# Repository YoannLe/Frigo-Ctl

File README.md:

# Frigo-Ctl
Arduino controller and thermostat with touch screen for 12V Fridge Compressor. Boat, RV, motorhome. To drive Danfoss, SECOP, vitrifrigo, 101N0212 compressors control units.

Compressors RPM, start and stop could be controled by resistors values and mechanical thermostat.

To set the best ratio between compressor speed and cold generation needed, the AOE protocol was developed on high end devices. This project coud genarate AOE control on a standard unit and specials functions like manual boost, graphic touch screen and DS18B20 temperature sensors.

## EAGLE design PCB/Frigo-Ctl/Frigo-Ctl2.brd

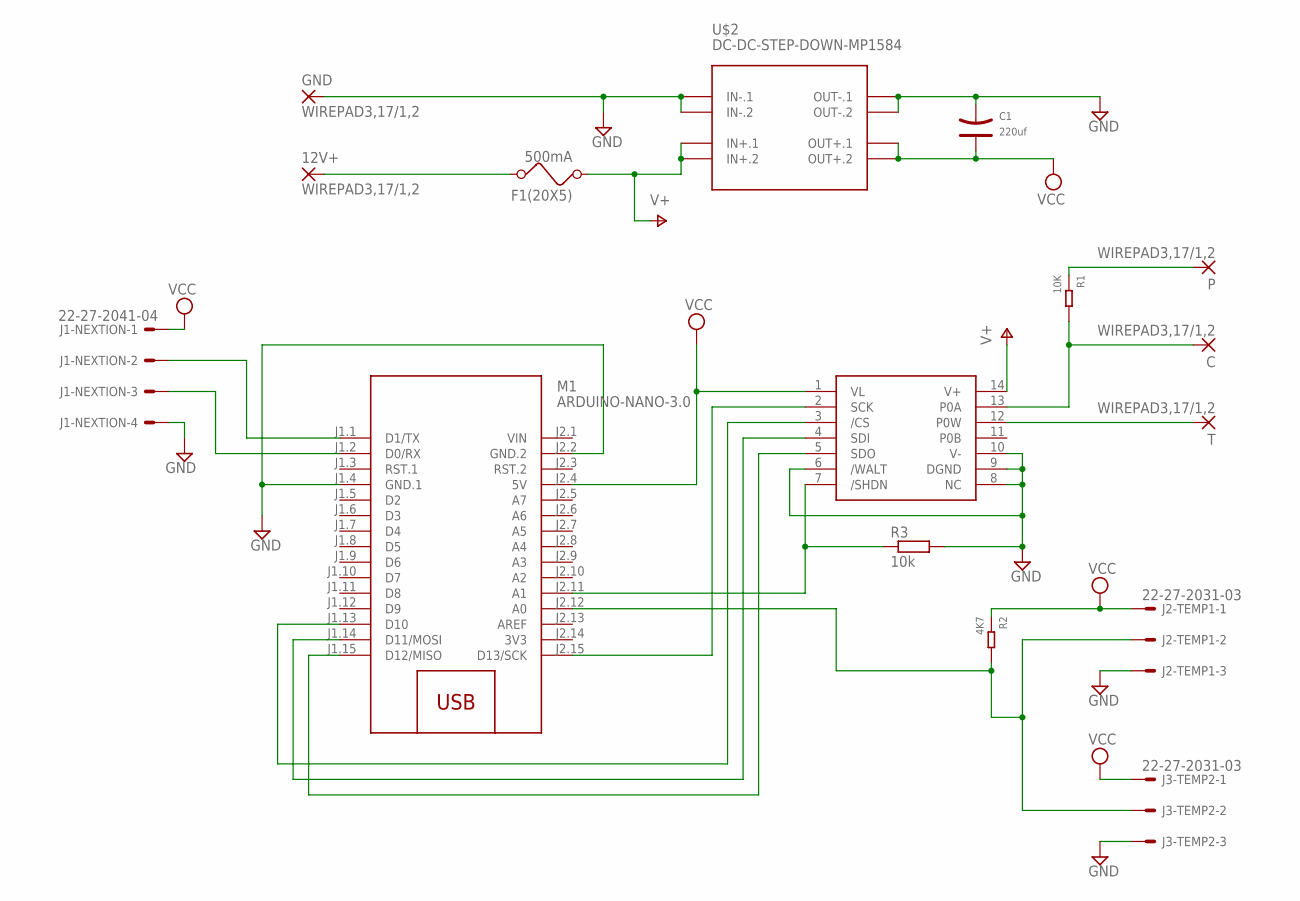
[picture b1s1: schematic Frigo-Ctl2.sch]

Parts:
12V+: WIREPAD3,17/1,2; 3,17/1,2
C: WIREPAD3,17/1,2; 3,17/1,2
C1: 220uf; PC-D5.3MM
F1(20X5): 500mA; FUSE
GND: WIREPAD3,17/1,2; 3,17/1,2
J1-NEXTION: 22-27-2041-04; 6410-04
J2-TEMP1, J3-TEMP2: 22-27-2031-03; 6410-03
M1: ARDUINO-NANO-3.0
P: WIREPAD3,17/1,2; 3,17/1,2
R1: 10K; PR-D2.3XL6.5MM
R2: 4K7; PR-D2.3XL6.5MM
R3: 10k; R1206
T: WIREPAD3,17/1,2; 3,17/1,2
U$1: MCP41HV51; TSSOP14
U$2: DC-DC-STEP-DOWN-MP1584

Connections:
3V3: M1.J2.14 (3V3)
GND: C1.-, GND.1, J1-NEXTION.4, J2-TEMP1.3, J3-TEMP2.3, M1.J1.4 (GND.1), M1.J2.2 (GND.2), R3.2, U$1.6 (/WALT), U$1.8 (NC), U$1.9 (DGND), U$1.10 (V-), U$2.IN-.1, U$2.IN-.2, U$2.OUT-.1, U$2.OUT-.2
unnamed: 12V+.1, F1(20X5).2
unnamed: M1.J2.11 (A1), R3.1, U$1.7 (/SHDN)
unnamed: J1-NEXTION.2, M1.J1.1 (D1/TX)
unnamed: J1-NEXTION.3, M1.J1.2 (D0/RX)
unnamed: C.1, R1.2, U$1.13 (P0A)
unnamed: P.1, R1.1
unnamed: M1.J1.13 (D10), U$1.3 (/CS)
unnamed: T.1, U$1.12 (P0W)
unnamed: M1.J2.15 (D13/SCK), U$1.2 (SCK)
unnamed: M1.J1.15 (D12/MISO), U$1.5 (SDO)
unnamed: M1.J1.14 (D11/MOSI), U$1.4 (SDI)
unnamed: J2-TEMP1.2, J3-TEMP2.2, M1.J2.12 (A0), R2.2
V+: F1(20X5).1, U$1.14 (V+), U$2.IN+.1, U$2.IN+.2
VCC: C1.+, J1-NEXTION.1, J2-TEMP1.1, J3-TEMP2.1, M1.J2.4 (5V), R2.1, U$1.1 (VL), U$2.OUT+.1, U$2.OUT+.2
VIN: M1.J2.1 (VIN)

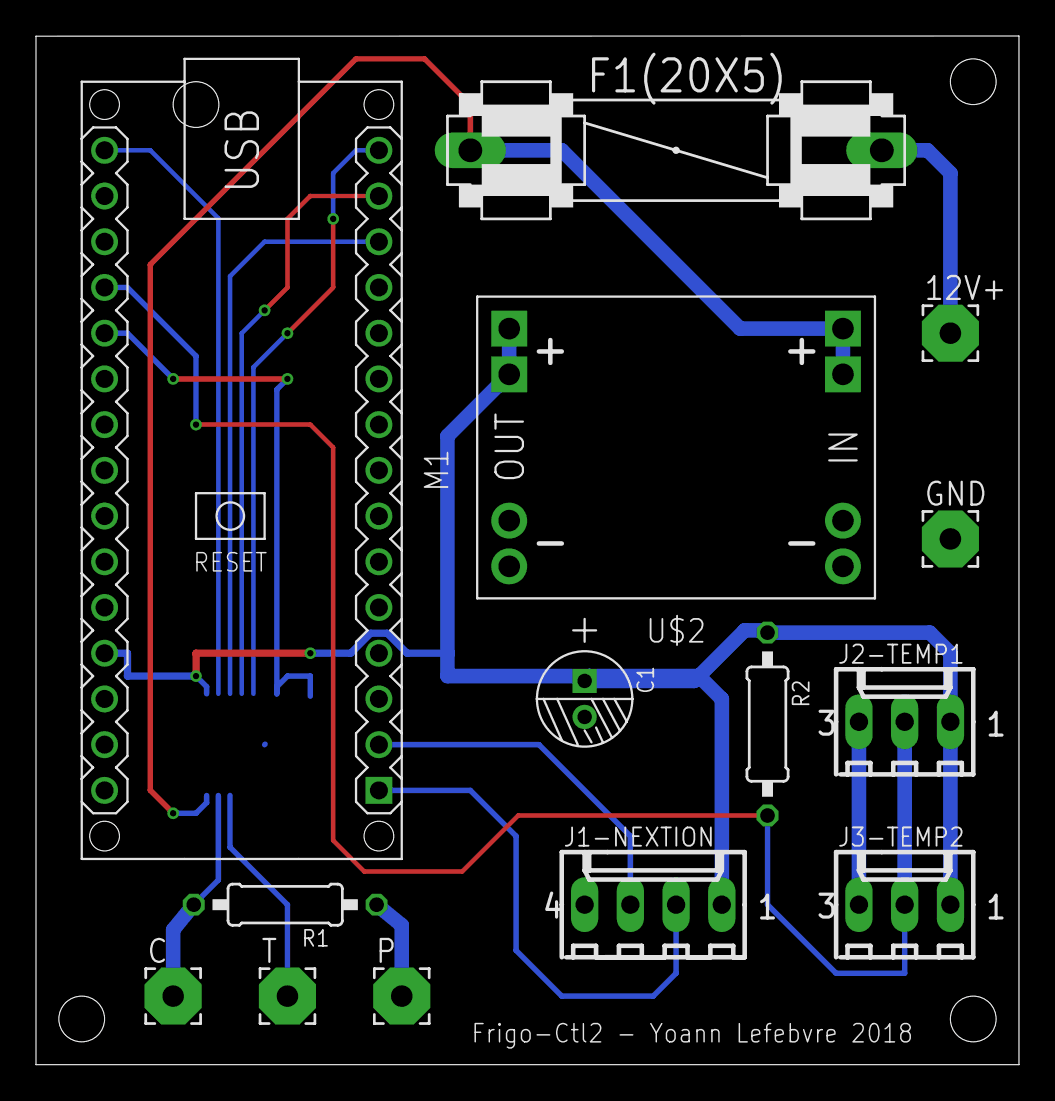
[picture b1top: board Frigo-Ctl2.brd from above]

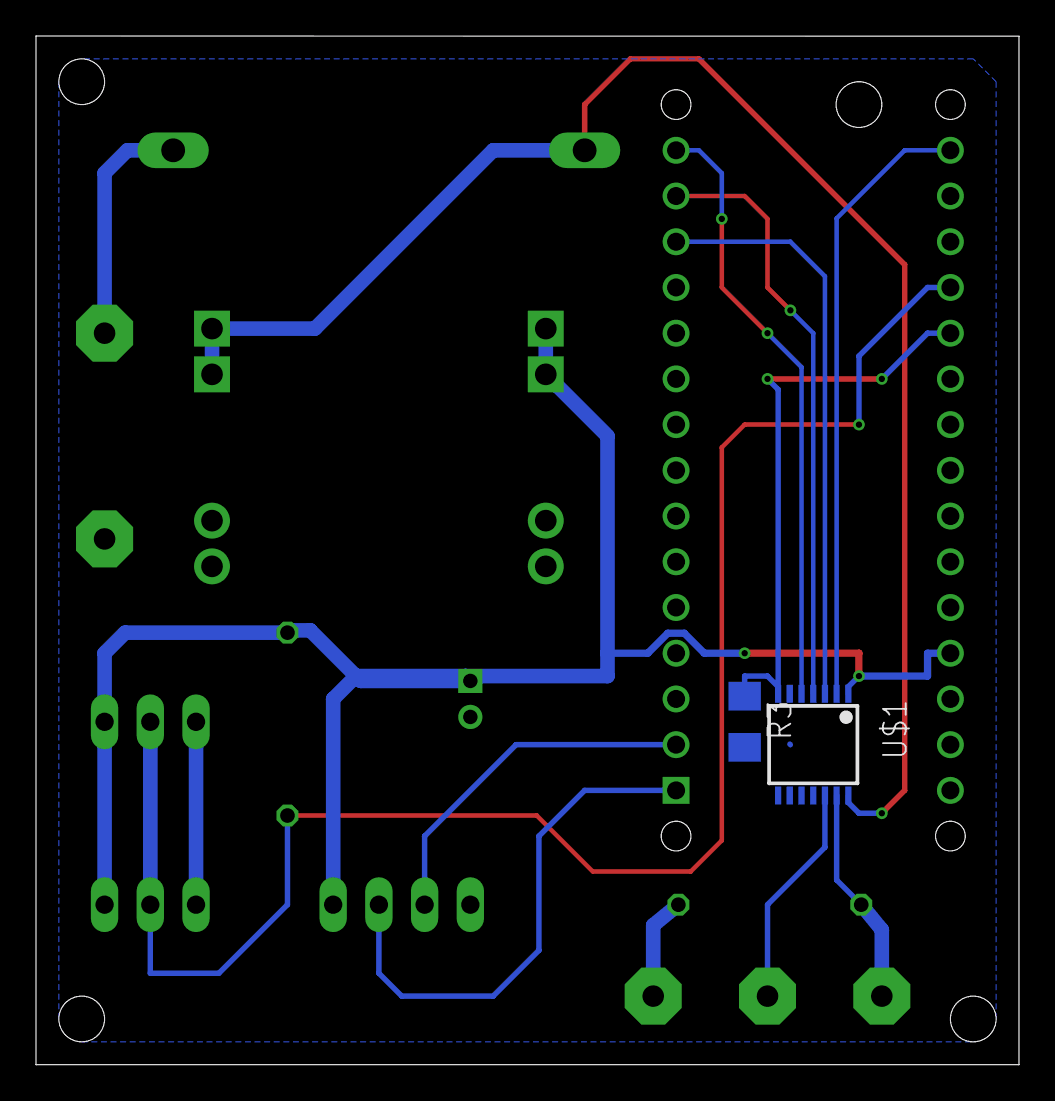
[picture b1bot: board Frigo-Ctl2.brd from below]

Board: 2 copper layers, 54.6 x 57.1 mm, 16 parts (2 on the bottom side), 15 nets.

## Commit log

2018-05-18 First upload, board schematic, PCB, Gerber and datasheets
2018-07-03 Pictures of PCB
2018-08-06 Last version with graph

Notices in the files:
parts and their libraries:
diy-modules: Released under the Creative Commons Attribution 4.0 International License: http://creativecommons.org/licenses/by/4.0
